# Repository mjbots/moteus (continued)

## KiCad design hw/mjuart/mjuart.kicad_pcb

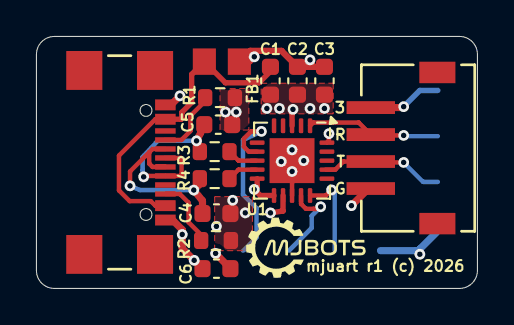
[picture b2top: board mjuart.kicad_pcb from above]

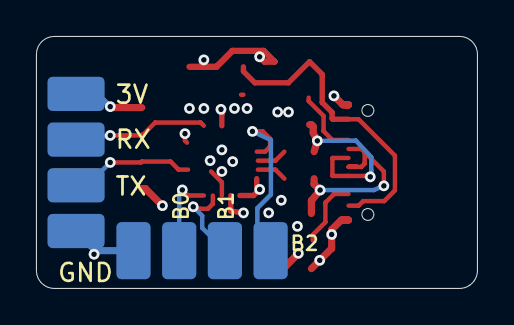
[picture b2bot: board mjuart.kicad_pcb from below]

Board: 4 copper layers, 24.5 x 14.0 mm, 16 parts (2 on the bottom side), 15 nets.

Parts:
C1: 10nF; C_0603_1608Metric
C2, C6: 100nF; C_0603_1608Metric
C3: 4.7uF; C_0603_1608Metric
C4, C5: 22pF; C_0603_1608Metric
FB1: FerriteBead; FB_MI0805K400R-10
J1: S4B-ZR-SM4A-TFLFSN; CONN_S4B-ZR-SM4A-TF_JST
J2: USB4110-GF-A; USB4110-GF-A_GCT
J3, J4: Conn_01x04_Pin; testpad4
R1, R2: 5.1k; R_0603_1608Metric
R3, R4: 27; R_0603_1608Metric
U1: FT231XQ; QFN-20-1EP_4x4mm_P0.5mm_EP2.5x2.5mm

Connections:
+3V: C6.1, J1.4, J3.4, U1.10 (3V3OUT), U1.11 (~RESET), U1.20 (VCCIO)
+5V: C2.1, C3.1, FB1.2, U1.12 (VCC)
/Power Input/USBC_N: C4.1, J2.A7 (DN1), J2.B7 (DN2), R4.1
/Power Input/USBC_P: C5.1, J2.A6 (DP1), J2.B6 (DP2), R3.1
/Power Input/USBDN: R4.2, U1.9 (USBDM)
/Power Input/USBDP: R3.2, U1.8 (USBDP)
GND: C1.2, C2.2, C3.2, C4.2, C5.2, C6.2, J1.1, J2.A1-B12 (GND), J2.A12-B1 (GND), J3.1, J4.1, R1.2, R2.2, U1.3 (GND), U1.13 (GND), U1.21 (GND)
unnamed: C1.1, FB1.1, J2.A4-B9 (VBUS), J2.A9-B4 (VBUS)
unnamed: J2.A5 (CC1), R1.1
unnamed: J2.B5 (CC2), R2.1
unnamed: J1.2, J3.2, U1.17 (TXD)
unnamed: J1.3, J3.3, U1.1 (RXD)
unnamed: J4.2, U1.15 (CBUS0)
unnamed: J4.3, U1.14 (CBUS1)
unnamed: J4.4, U1.7 (CBUS2)

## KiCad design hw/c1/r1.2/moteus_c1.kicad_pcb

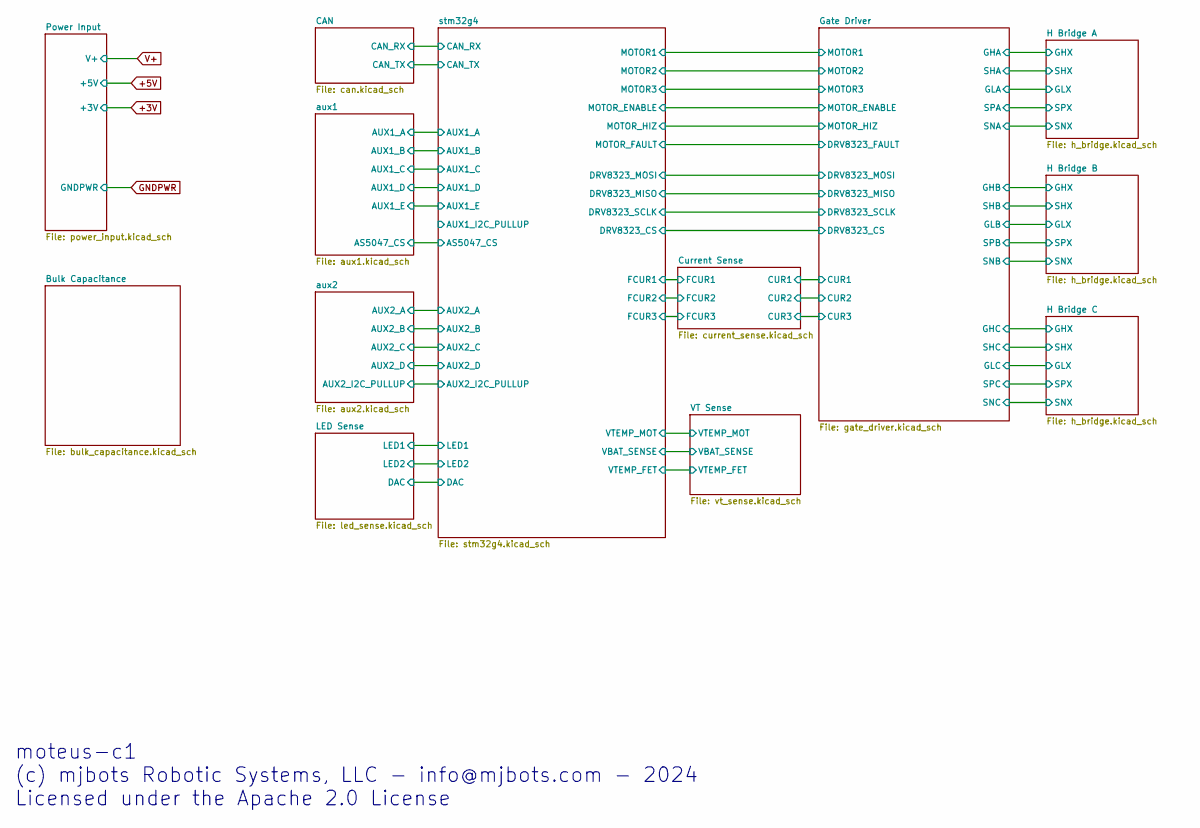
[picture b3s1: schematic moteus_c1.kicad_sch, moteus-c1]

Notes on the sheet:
moteus-c1 (c) mjbots Robotic Systems, LLC - info@mjbots.com - 2024 Licensed under the Apache 2.0 License

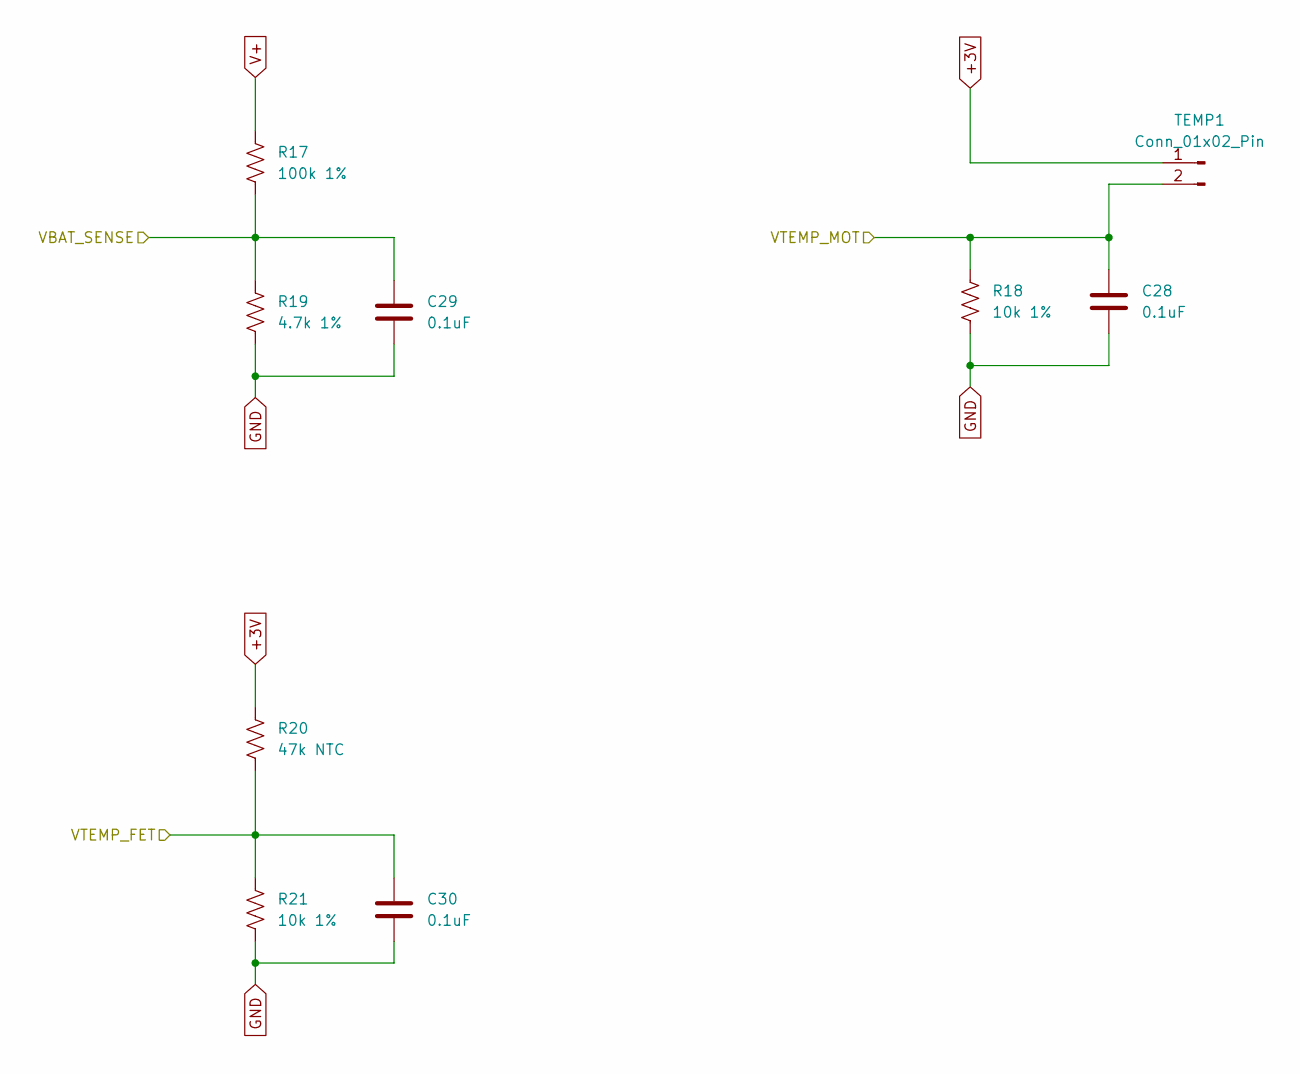
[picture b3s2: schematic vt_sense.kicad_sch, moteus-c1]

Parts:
C28, C29, C30: 0.1uF; C_0402_1005Metric; MPN MF-CAP-0402-0.1uF
R17: 100k 1%; R_0402_1005Metric; MPN RC0402FR-07100KL
R18, R21: 10k 1%; R_0402_1005Metric; MPN RC0402FR-0710KL
R19: 4.7k 1%; R_0402_1005Metric; MPN RC0402FR-074K7L
R20: 47k NTC; R_0402_1005Metric; MPN NCP15WB473F03RC
TEMP1: Conn_01x02_Pin; PinHeader_1x02_P2.00mm_Vertical

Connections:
/VT Sense/VBAT_SENSE: C29.1, R17.2, R19.1; also elsewhere on the board
/VT Sense/VTEMP_FET: C30.1, R20.2, R21.1; also elsewhere on the board
/VT Sense/VTEMP_MOT: C28.1, R18.1, TEMP1.2; also elsewhere on the board
V+: R17.1; also elsewhere on the board

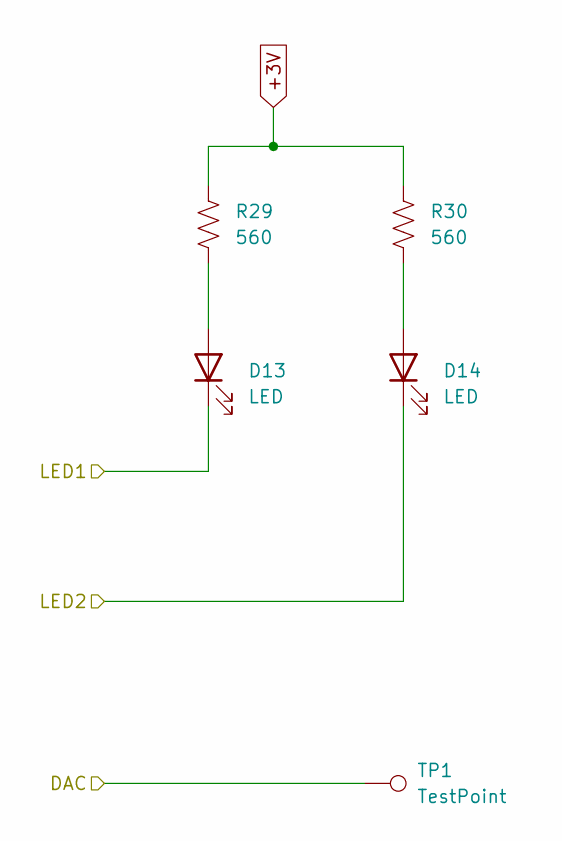
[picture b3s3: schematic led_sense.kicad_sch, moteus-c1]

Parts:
D13: LED; LED_0603_1608Metric; MPN MF-LED-0603-RED
D14: LED; LED_0603_1608Metric; MPN MF-LED-0603-GREEN
R29, R30: 560; R_0402_1005Metric; MPN MF-RES-0402-560
TP1: TestPoint; TestPoint_THTPad_D1.0mm_Drill0.5mm

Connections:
/LED Sense/LED1: D13.1 (K); also elsewhere on the board
/LED Sense/LED2: D14.1 (K); also elsewhere on the board
unnamed: D13.2 (A), R29.2
unnamed: D14.2 (A), R30.2

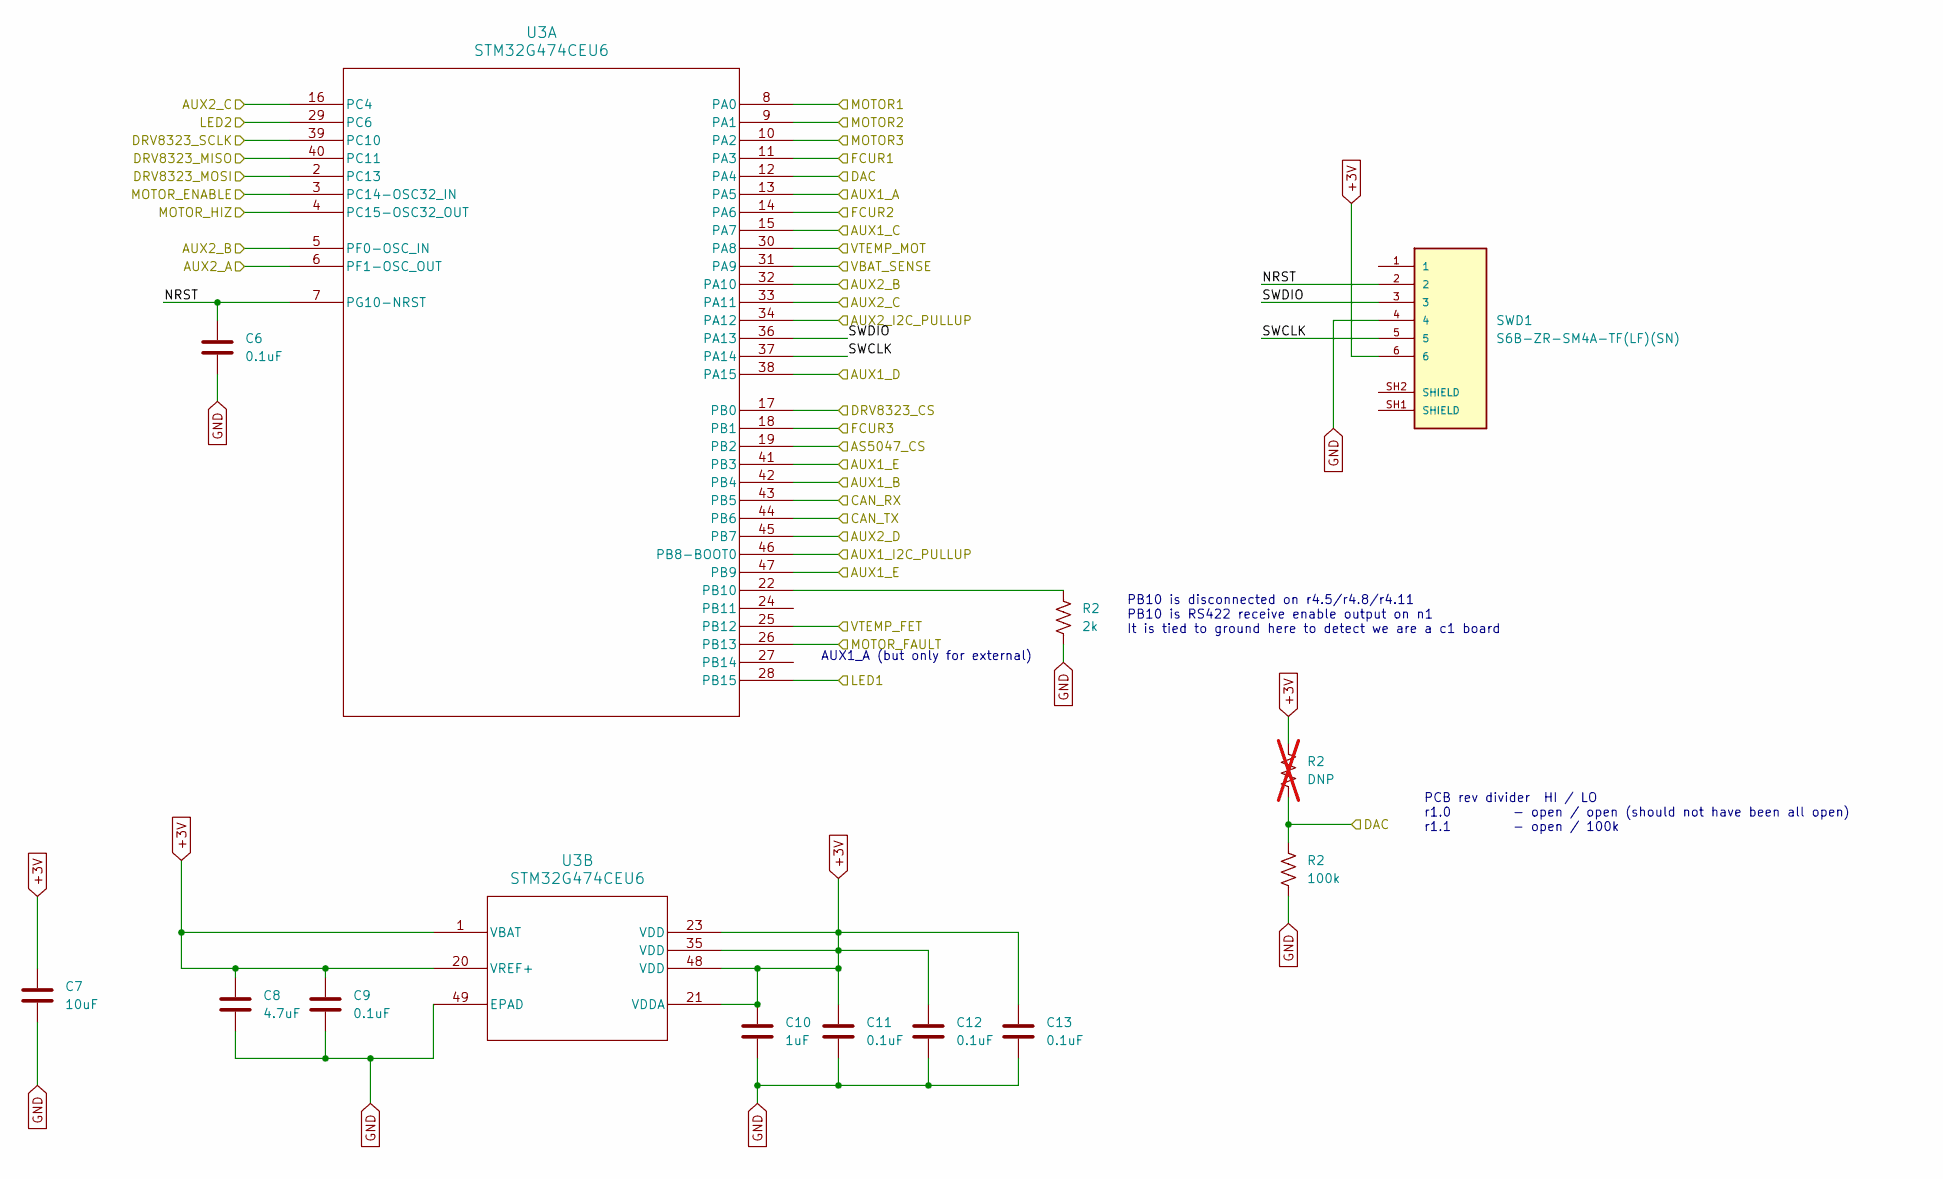
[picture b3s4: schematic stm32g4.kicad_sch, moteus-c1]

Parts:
C6, C9, C11, C12, C13: 0.1uF; C_0402_1005Metric; MPN MF-CAP-0402-0.1uF
C7: 10uF; C_1206_3216Metric; MPN MF-CAP-1206-10uF
C8: 4.7uF; C_0603_1608Metric; MPN CL10A475KP8NNNC
C10: 1uF; C_0402_1005Metric; MPN MF-CAP-0402-1uF
R2: 2k; R_0402_1005Metric; MPN MF-RES-0402-2K
SWD1: S6B-ZR-SM4A-TF(LF)(SN); JST_S6B-ZR-SM4A-TF(LF)(SN); MPN S6B-ZR-SM4A-TF(LF)(SN)
U3: STM32G474CEU6; UFQFPN-48_7X7X0P55MM; MPN STM32G474CEU6

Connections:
/CAN/CAN_RX: U3.43 (PB5); also elsewhere on the board
/CAN/CAN_TX: U3.44 (PB6); also elsewhere on the board
/Current Sense/FCUR1: U3.11 (PA3); also elsewhere on the board
/Current Sense/FCUR2: U3.14 (PA6); also elsewhere on the board
/Current Sense/FCUR3: U3.18 (PB1); also elsewhere on the board
/Gate Driver/DRV8323_CS: U3.17 (PB0); also elsewhere on the board
/Gate Driver/DRV8323_FAULT: U3.26 (PB13); also elsewhere on the board
/Gate Driver/DRV8323_MOSI: U3.2 (PC13); also elsewhere on the board
/Gate Driver/DRV8323_SCLK: U3.39 (PC10); also elsewhere on the board
/Gate Driver/MOTOR1: U3.8 (PA0); also elsewhere on the board
/Gate Driver/MOTOR2: U3.9 (PA1); also elsewhere on the board
/Gate Driver/MOTOR3: U3.10 (PA2); also elsewhere on the board
/Gate Driver/MOTOR_ENABLE: U3.3 (PC14-OSC32_IN); also elsewhere on the board
/Gate Driver/MOTOR_HIZ: U3.4 (PC15-OSC32_OUT); also elsewhere on the board
/LED Sense/LED1: U3.28 (PB15); also elsewhere on the board
/LED Sense/LED2: U3.29 (PC6); also elsewhere on the board
/VT Sense/VBAT_SENSE: U3.31 (PA9); also elsewhere on the board
/VT Sense/VTEMP_FET: U3.25 (PB12); also elsewhere on the board
/VT Sense/VTEMP_MOT: U3.30 (PA8); also elsewhere on the board
/aux1/AS5047_CS: U3.19 (PB2); also elsewhere on the board
/aux1/AUX1_A: U3.13 (PA5); also elsewhere on the board
/aux1/AUX1_B: U3.42 (PB4); also elsewhere on the board
/aux1/AUX1_C: U3.15 (PA7); also elsewhere on the board
/aux1/AUX1_D: U3.38 (PA15); also elsewhere on the board
/aux1/AUX1_E: U3.41 (PB3), U3.47 (PB9); also elsewhere on the board
/aux2/AUX2_A: U3.6 (PF1-OSC_OUT); also elsewhere on the board
/aux2/AUX2_B: U3.5 (PF0-OSC_IN), U3.32 (PA10); also elsewhere on the board
/aux2/AUX2_C: U3.16 (PC4), U3.33 (PA11); also elsewhere on the board
/aux2/AUX2_D: U3.45 (PB7); also elsewhere on the board
/aux2/AUX2_I2C_PULLUP: U3.34 (PA12); also elsewhere on the board
/stm32g4/AUX1_I2C_PULLUP: U3.46 (PB8-BOOT0)
/stm32g4/NRST: C6.1, SWD1.2, U3.7 (PG10-NRST)
/stm32g4/SWCLK: SWD1.5, U3.37 (PA14)
/stm32g4/SWDIO: SWD1.3, U3.36 (PA13)

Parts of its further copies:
R31: 2k; R_0402_1005Metric; MPN MF-RES-0402-2K

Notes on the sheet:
PB10 is disconnected on r4.5/r4.8/r4.11 PB10 is RS422 receive enable output on n1 It is tied to ground here to detect we are a c1 board
PCB rev divider HI / LO r1.0 - open / open (should not have been all open) r1.1 - open / 100k
AUX1_A (but only for external)

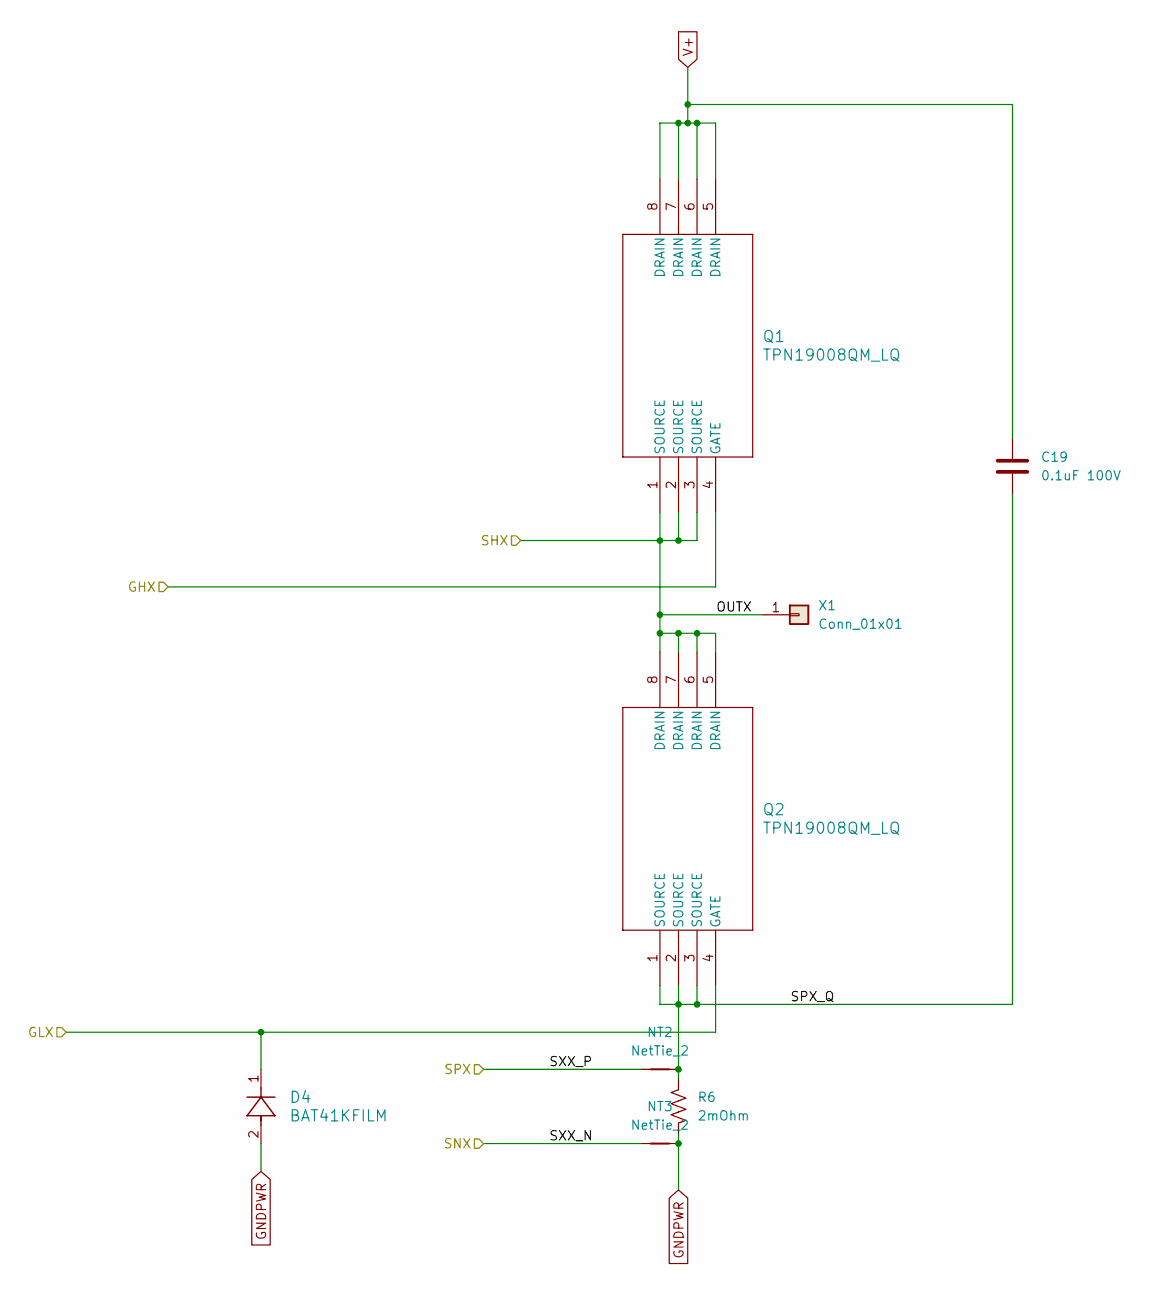
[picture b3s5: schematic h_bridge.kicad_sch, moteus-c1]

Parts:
C19: 0.1uF 100V; C_1206_3216Metric; MPN 12061C104KAT2A
D4: BAT41KFILM; SOD-523_STM; MPN BAT41KFILM
NT2, NT3: NetTie_2; NetTie-2_SMD_Pad0.2
Q1, Q2: TPN19008QM_LQ; TSON Advance_TOS; MPN TPN19008QM,LQ
R6: 2mOhm; R_0805_2012Metric; MPN CSSH0805FT2L00
X1: Conn_01x01; POWER_M2.5

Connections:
/Gate Driver/GHA: Q1.4 (GATE); also elsewhere on the board
/Gate Driver/GLA: D4.1, Q2.4 (GATE); also elsewhere on the board
/H Bridge A/OUTX: Q1.1 (SOURCE), Q1.2 (SOURCE), Q1.3 (SOURCE), Q2.5 (DRAIN), Q2.6 (DRAIN), Q2.7 (DRAIN), Q2.8 (DRAIN), X1.1; also elsewhere on the board
/H Bridge A/SPX_Q: C19.2, NT2.2, Q2.1 (SOURCE), Q2.2 (SOURCE), Q2.3 (SOURCE), R6.1
/H Bridge A/SXX_N: NT3.1; also elsewhere on the board
/H Bridge A/SXX_P: NT2.1; also elsewhere on the board
GNDPWR: D4.2, NT3.2, R6.2; also elsewhere on the board
V+: C19.1, Q1.5 (DRAIN), Q1.6 (DRAIN), Q1.7 (DRAIN), Q1.8 (DRAIN); also elsewhere on the board

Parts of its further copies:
C20, C21: 0.1uF 100V; C_1206_3216Metric; MPN 12061C104KAT2A
D7, D10: BAT41KFILM; SOD-523_STM; MPN BAT41KFILM
NT4, NT5, NT6, NT7: NetTie_2; NetTie-2_SMD_Pad0.2
Q3, Q4, Q5, Q6: TPN19008QM_LQ; TSON Advance_TOS; MPN TPN19008QM,LQ
R9, R12: 2mOhm; R_0805_2012Metric; MPN CSSH0805FT2L00
X2, X3: Conn_01x01; POWER_M2.5

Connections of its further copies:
/Gate Driver/GHB: Q3.4 (GATE); also elsewhere on the board
/Gate Driver/GHC: Q5.4 (GATE); also elsewhere on the board
/Gate Driver/GLB: D7.1, Q4.4 (GATE); also elsewhere on the board
/Gate Driver/GLC: D10.1, Q6.4 (GATE); also elsewhere on the board
/H Bridge B/OUTX: Q3.1 (SOURCE), Q3.2 (SOURCE), Q3.3 (SOURCE), Q4.5 (DRAIN), Q4.6 (DRAIN), Q4.7 (DRAIN), Q4.8 (DRAIN), X2.1; also elsewhere on the board
/H Bridge B/SPX_Q: C20.2, NT4.2, Q4.1 (SOURCE), Q4.2 (SOURCE), Q4.3 (SOURCE), R9.1
/H Bridge B/SXX_N: NT5.1; also elsewhere on the board
/H Bridge B/SXX_P: NT4.1; also elsewhere on the board
/H Bridge C/OUTX: Q5.1 (SOURCE), Q5.2 (SOURCE), Q5.3 (SOURCE), Q6.5 (DRAIN), Q6.6 (DRAIN), Q6.7 (DRAIN), Q6.8 (DRAIN), X3.1; also elsewhere on the board
/H Bridge C/SPX_Q: C21.2, NT6.2, Q6.1 (SOURCE), Q6.2 (SOURCE), Q6.3 (SOURCE), R12.1
/H Bridge C/SXX_N: NT7.1; also elsewhere on the board
/H Bridge C/SXX_P: NT6.1; also elsewhere on the board
GNDPWR: D7.2, D10.2, NT5.2, NT7.2, R9.2, R12.2; also elsewhere on the board
V+: C20.1, C21.1, Q3.5 (DRAIN), Q3.6 (DRAIN), Q3.7 (DRAIN), Q3.8 (DRAIN), Q5.5 (DRAIN), Q5.6 (DRAIN), Q5.7 (DRAIN), Q5.8 (DRAIN); also elsewhere on the board

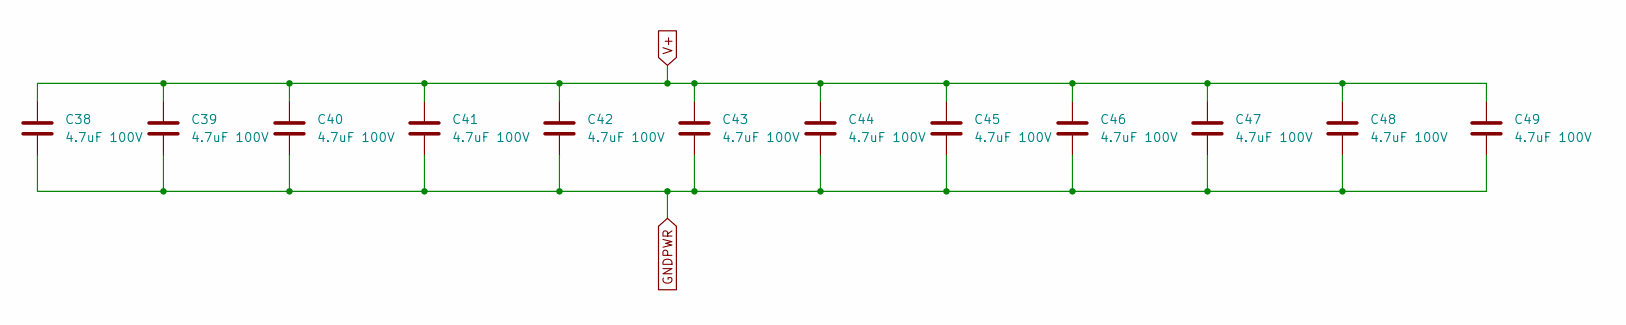
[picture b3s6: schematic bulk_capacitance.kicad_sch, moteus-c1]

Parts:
C38, C39, C40, C41, C42, C43, C44, C45, C46, C47, C48, C49: 4.7uF 100V; C_1206_3216Metric; MPN GRJ31CC72A475KE01K

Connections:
GNDPWR: C38.2, C39.2, C40.2, C41.2, C42.2, C43.2, C44.2, C45.2, C46.2, C47.2, C48.2, C49.2; also elsewhere on the board
V+: C38.1, C39.1, C40.1, C41.1, C42.1, C43.1, C44.1, C45.1, C46.1, C47.1, C48.1, C49.1; also elsewhere on the board

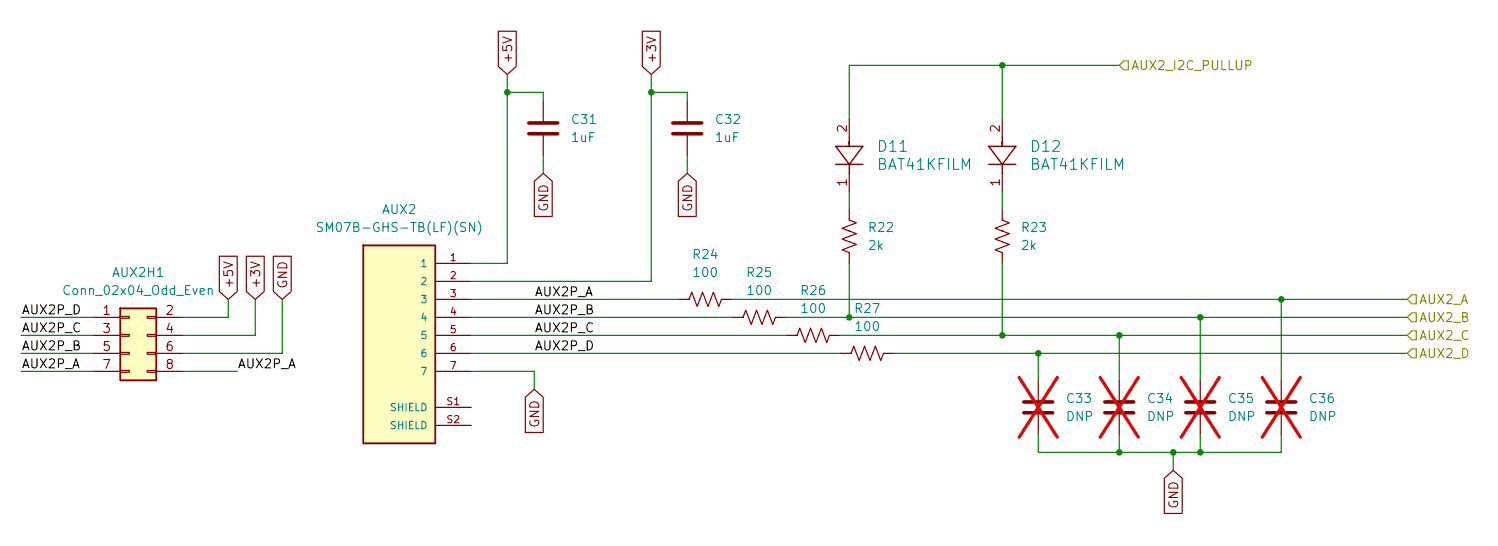
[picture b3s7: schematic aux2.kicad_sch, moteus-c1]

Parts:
AUX2: SM07B-GHS-TB(LF)(SN); JST_SM07B-GHS-TB(LF)(SN); MPN SM07B-GHS-TB(LF)(SN)
AUX2H1: Conn_02x04_Odd_Even; PinHeader_2x04_P1.27mm_Vertical
C31, C32: 1uF; C_0402_1005Metric; MPN MF-CAP-0402-1uF
C33, C34, C35, C36: DNP; C_0402_1005Metric; not fitted
D11, D12: BAT41KFILM; SOD-523_STM; MPN BAT41KFILM
R22, R23: 2k; R_0402_1005Metric; MPN MF-RES-0402-2K
R24, R25, R26, R27: 100; R_0402_1005Metric; MPN MF-RES-0402-100

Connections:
+5V: AUX2.1, AUX2H1.2, C31.1; also elsewhere on the board
/aux2/AUX2P_B: AUX2.4, AUX2H1.5, R25.1
/aux2/AUX2P_C: AUX2.5, AUX2H1.3, R26.1
/aux2/AUX2P_D: AUX2.6, AUX2H1.1, R27.1
/aux2/AUX2_A: C36.1, R24.2; also elsewhere on the board
/aux2/AUX2_B: C35.1, R22.2, R25.2; also elsewhere on the board
/aux2/AUX2_C: C34.1, R23.2, R26.2; also elsewhere on the board
/aux2/AUX2_D: C33.1, R27.2; also elsewhere on the board
/aux2/AUX2_I2C_PULLUP: D11.2, D12.2; also elsewhere on the board
unnamed: D11.1, R22.1
unnamed: D12.1, R23.1

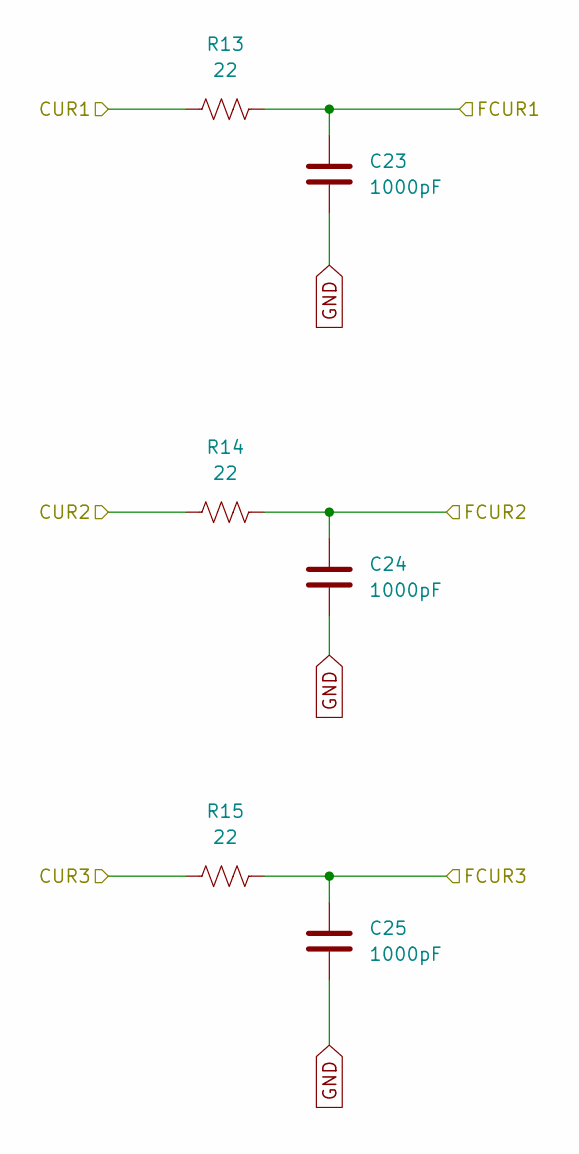
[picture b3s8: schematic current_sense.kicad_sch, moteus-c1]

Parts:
C23, C24, C25: 1000pF; C_0402_1005Metric; MPN MF-CAP-0402-1nF
R13, R14, R15: 22; R_0402_1005Metric; MPN MF-RES-0402-22

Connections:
/Current Sense/CUR1: R13.1; also elsewhere on the board
/Current Sense/CUR2: R14.1; also elsewhere on the board
/Current Sense/CUR3: R15.1; also elsewhere on the board
/Current Sense/FCUR1: C23.1, R13.2; also elsewhere on the board
/Current Sense/FCUR2: C24.1, R14.2; also elsewhere on the board
/Current Sense/FCUR3: C25.1, R15.2; also elsewhere on the board

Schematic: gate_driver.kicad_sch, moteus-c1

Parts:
C14: 1uF 25V; C_0603_1608Metric; MPN C1608X7R1E105K080AE
C15: 0.1uF 100V; C_0603_1608Metric; MPN GCJ188R72A104KA01D
C16: 47nF 100V; C_0603_1608Metric; MPN C0603X473K1RAC7867
C17: 1uF; C_0402_1005Metric; MPN MF-CAP-0402-1uF
C18: 1uF; C_0603_1608Metric; MPN MF-CAP-0603-1uF
R2, R3: 2k; R_0402_1005Metric; MPN MF-RES-0402-2K
U4: DRV8323SRTAR; RTA0040B; MPN DRV8323SRTAR

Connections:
/Current Sense/CUR1: U4.21 (SOC); also elsewhere on the board
/Current Sense/CUR2: U4.22 (SOB); also elsewhere on the board
/Current Sense/CUR3: U4.23 (SOA); also elsewhere on the board
/Gate Driver/DRV8323_CS: U4.29 (GAIN_SCS_N); also elsewhere on the board
/Gate Driver/DRV8323_FAULT: R3.2, U4.25 (FAULT_N); also elsewhere on the board
/Gate Driver/DRV8323_MOSI: U4.27 (IDRIVE_SDI); also elsewhere on the board
/Gate Driver/DRV8323_SCLK: U4.28 (VDS_SCLK); also elsewhere on the board
/Gate Driver/GHA: U4.6 (GHA); also elsewhere on the board
/Gate Driver/GHB: U4.15 (GHB); also elsewhere on the board
/Gate Driver/GHC: U4.16 (GHC); also elsewhere on the board
/Gate Driver/GLA: U4.8 (GLA); also elsewhere on the board
/Gate Driver/GLB: U4.13 (GLB); also elsewhere on the board
/Gate Driver/GLC: U4.18 (GLC); also elsewhere on the board
/Gate Driver/MOTOR1: U4.34 (INHA); also elsewhere on the board
/Gate Driver/MOTOR2: U4.36 (INHB); also elsewhere on the board
/Gate Driver/MOTOR3: U4.38 (INHC); also elsewhere on the board
/Gate Driver/MOTOR_ENABLE: U4.30 (ENABLE); also elsewhere on the board
/Gate Driver/MOTOR_HIZ: U4.35 (INLA), U4.37 (INLB), U4.39 (INLC); also elsewhere on the board
/H Bridge A/OUTX: U4.7 (SHA); also elsewhere on the board
/H Bridge A/SXX_N: U4.10 (SNA); also elsewhere on the board
/H Bridge A/SXX_P: U4.9 (SPA); also elsewhere on the board
/H Bridge B/OUTX: U4.14 (SHB); also elsewhere on the board
/H Bridge B/SXX_N: U4.11 (SNB); also elsewhere on the board
/H Bridge B/SXX_P: U4.12 (SPB); also elsewhere on the board
/H Bridge C/OUTX: U4.17 (SHC); also elsewhere on the board
/H Bridge C/SXX_N: U4.20 (SNC); also elsewhere on the board
/H Bridge C/SXX_P: U4.19 (SPC); also elsewhere on the board
GNDPWR: C15.1, U4.40 (PGND), U4.41 (PAD); also elsewhere on the board
unnamed: C16.2, U4.2 (CPH)
unnamed: C16.1, U4.1 (CPL)
unnamed: C17.2, U4.33 (DVDD)
unnamed: C14.2, U4.3 (VCP)
V+: C14.1, C15.2, U4.4 (VM), U4.5 (VDRAIN); also elsewhere on the board

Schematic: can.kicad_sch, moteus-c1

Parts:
C26, C27: 0.1uF; C_0402_1005Metric; MPN MF-CAP-0402-0.1uF
CAN1: S3B-PH-SM4-TB(LF)(SN); JST_S3B-PH-SM4-TB(LF)(SN); MPN S3B-PH-SM4-TB(LF)(SN)
CAN_DBG1: Conn_01x03_Pin; PinHeader_1x03_P2.00mm_Vertical
R16: 120; R_0603_1608Metric; MPN RC0805FR-07120RL; not fitted
U5: TCAN1057AEV-Q1; SOIC-8_3.9x4.9mm_P1.27mm; MPN TCAN1057AEVDRQ1

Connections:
+5V: C27.1, U5.3 (VCC); also elsewhere on the board
/CAN/CAN_N: CAN1.2, CAN_DBG1.2, R16.2, U5.6 (CANL)
/CAN/CAN_P: CAN1.1, CAN_DBG1.1, R16.1, U5.7 (CANH)
/CAN/CAN_RX: U5.4 (RXD); also elsewhere on the board
/CAN/CAN_TX: U5.1 (TXD); also elsewhere on the board

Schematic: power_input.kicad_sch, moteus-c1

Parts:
C1: 1uF 100V; C_0805_2012Metric; MPN GCM21BC72A105KE36L
C2: 22uF; C_1206_3216Metric; MPN GRM31CR71A226KE15L
C3, C4: 1uF; C_0402_1005Metric; MPN MF-CAP-0402-1uF
C5: 1uF; C_0603_1608Metric; MPN MF-CAP-0603-1uF
C22: DNP; C_0402_1005Metric; not fitted
D1: SMBJ48D-M3/I; D_SMB; MPN SMBJ48D-M3/I
J1: XT30PW-M; AMASS_XT30PW-M; MPN XT30PW-M
L1: 47uH; IND_4018-WE-LQS_WRE; MPN 74404042470
NT1: NetTie_2; NetTie-2_SMD_Pad0.254mm
R1: 0; R_0402_1005Metric; MPN MF-RES-0402-0
R4: DNP; R_0402_1005Metric; not fitted
U1: MAX15062BATA+T; 21-0487A_MXM; MPN MAX15062BATA+T
U2: TLV70233PDBVR; SOT-23-5; MPN TLV70233PDBVR
VN1: Conn_01x01; POWER_M2.5
VP1: Conn_01x01; POWER_M2.5

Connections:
+5V: C2.1, C3.1, L1.1, U1.4 (FB/VOUT), U2.1 (IN), U2.3 (EN); also elsewhere on the board
GNDPWR: C1.2, C5.2, C22.2, D1.2 (A2), J1.N, NT1.1, R4.2, VN1.1; also elsewhere on the board
MOUNT_GND: C22.1, R4.1; also elsewhere on the board
unnamed: L1.2, U1.8 (LX)
unnamed: R1.1, U1.5 (MODE)
unnamed: C5.1, U1.3 (VCC)
V+: C1.1, D1.1 (A1), J1.P, U1.1 (VIN), U1.2 (EN/UVLO), VP1.1; also elsewhere on the board

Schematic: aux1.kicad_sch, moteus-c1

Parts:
AUX1: Conn_01x04; PinHeader_1x04_P1.27mm_Vertical
C37: 0.1uF; C_0402_1005Metric; MPN MF-CAP-0402-0.1uF
R24: 100; R_0402_1005Metric; MPN MF-RES-0402-100
R28: 0; R_0402_1005Metric; MPN MF-RES-0402-0
U6: AS5047P-ATSM; TSSOP14_OSM; MPN AS5047P-ATSM

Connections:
/aux1/AS5047_CS: U6.1 (CSn); also elsewhere on the board
/aux1/AUX1_A: U6.2 (CLK); also elsewhere on the board
/aux1/AUX1_B: U6.3 (MISO); also elsewhere on the board
/aux1/AUX1_C: U6.4 (MOSI); also elsewhere on the board
/aux2/AUX2_A: R24.2; also elsewhere on the board
unnamed: R28.1, U6.11 (VDD)

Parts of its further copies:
R34, R35: 100; R_0402_1005Metric; MPN MF-RES-0402-100

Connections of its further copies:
/aux1/AUX1_D: R34.2; also elsewhere on the board
/aux1/AUX1_E: R35.2; also elsewhere on the board

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
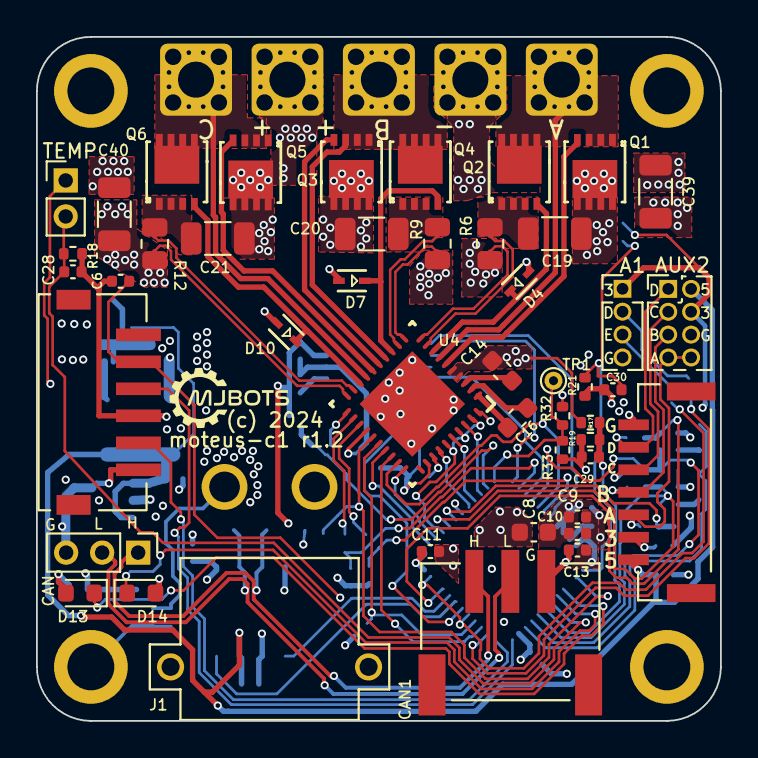
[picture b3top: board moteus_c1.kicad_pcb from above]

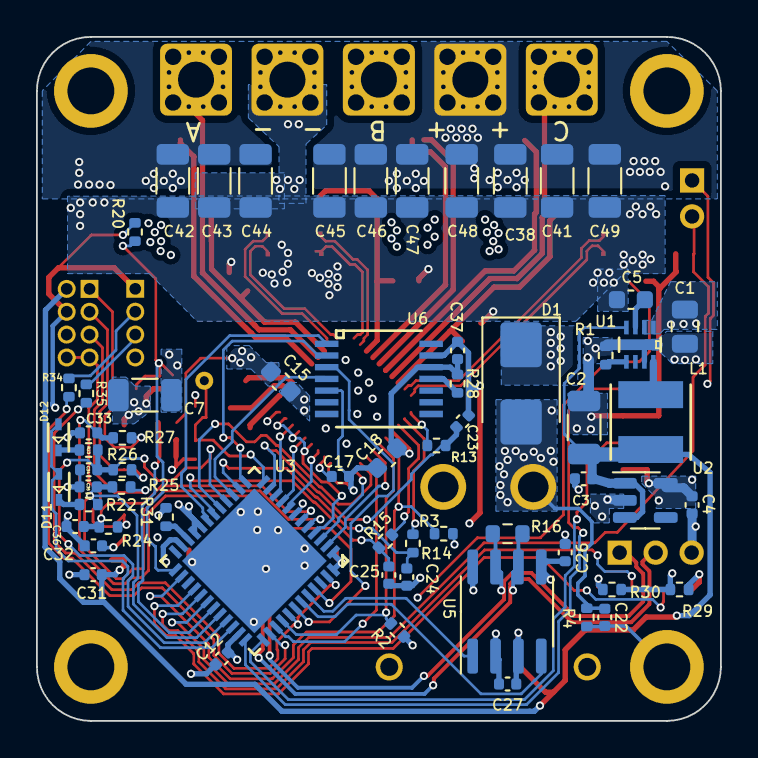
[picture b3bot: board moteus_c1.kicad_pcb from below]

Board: 4 copper layers, 38.0 x 38.0 mm, 125 parts (64 on the bottom side), 83 nets.

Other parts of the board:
MOUNT1, MOUNT2, MOUNT3, MOUNT4: M2.5_MOUNT
R32: DNP; R_0402_1005Metric
R33: 100k; R_0402_1005Metric

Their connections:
MOUNT_GND: MOUNT3.1; also elsewhere on the board
